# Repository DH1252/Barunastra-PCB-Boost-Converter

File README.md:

# Barunastra-PCB-Boost-Converter

This is an adjustable boost converter based on the LM2577 IC that can handle upto 2A

It features an adjustable output voltage, a output smoothing capacitor, and a LED indicator

It uses two screw terminals for input and output

The PCB is two layers and a track width of 0.7 mm to handle 2 Amps

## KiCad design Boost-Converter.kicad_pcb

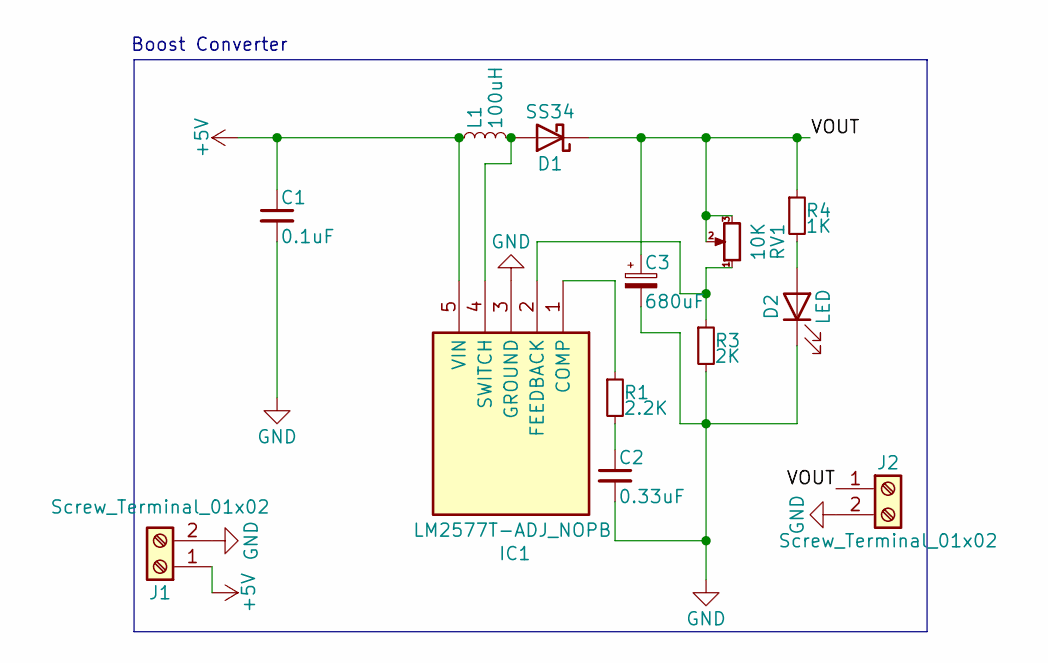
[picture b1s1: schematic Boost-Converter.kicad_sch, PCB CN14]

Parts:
C1: 0.1uF; C_0805_2012Metric
C2: 0.33uF; C_0805_2012Metric
C3: 680uF; CP_Elec_10x10
D1: SS34; D_SMA
D2: LED; LED_D3.0mm
IC1: LM2577T-ADJ_NOPB; TO-263-5_TabPin3; Manufacturer_Part_Number LM2577T-ADJ/NOPB; Mouser Part Number 926-LM2577T-ADJ/NOPB
J1, J2: Screw_Terminal_01x02; TerminalBlock_Xinya_XY308-2.54-2P_1x02_P2.54mm_Horizontal
L1: 100uH; SRR1260101M
R1: 2.2K; R_0805_2012Metric
R3: 2K; R_0805_2012Metric
R4: 1K; R_0805_2012Metric
RV1: 10K; 3313J1503E

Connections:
+5V: C1.1, IC1.5 (VIN), J1.1, L1.1
/VOUT: C3.1, D1.1 (K), J2.1, R4.1, RV1.2, RV1.3
GND: C1.2, C2.2, C3.2, D2.1 (K), IC1.3 (GROUND), J1.2, J2.2, R3.2
unnamed: C2.1, R1.2
unnamed: D1.2 (A), IC1.4 (SWITCH), L1.2
unnamed: D2.2 (A), R4.2
unnamed: IC1.1 (COMP), R1.1
unnamed: IC1.2 (FEEDBACK), R3.1, RV1.1

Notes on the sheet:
Boost Converter

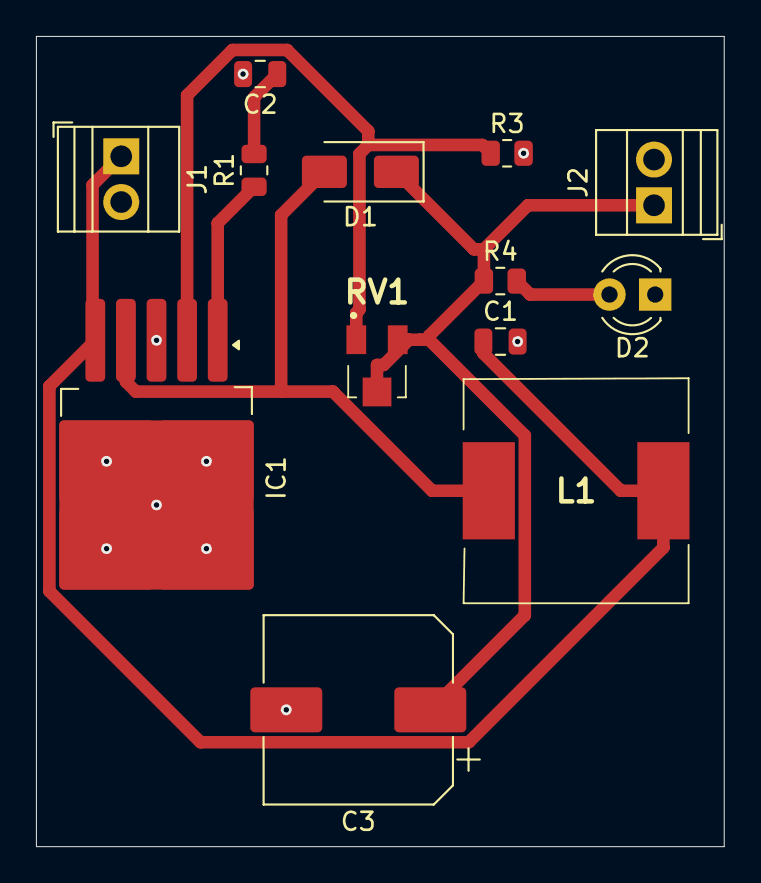
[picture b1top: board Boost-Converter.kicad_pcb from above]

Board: 2 copper layers, 38.2 x 45.0 mm, 13 parts (0 on the bottom side), 8 nets.
